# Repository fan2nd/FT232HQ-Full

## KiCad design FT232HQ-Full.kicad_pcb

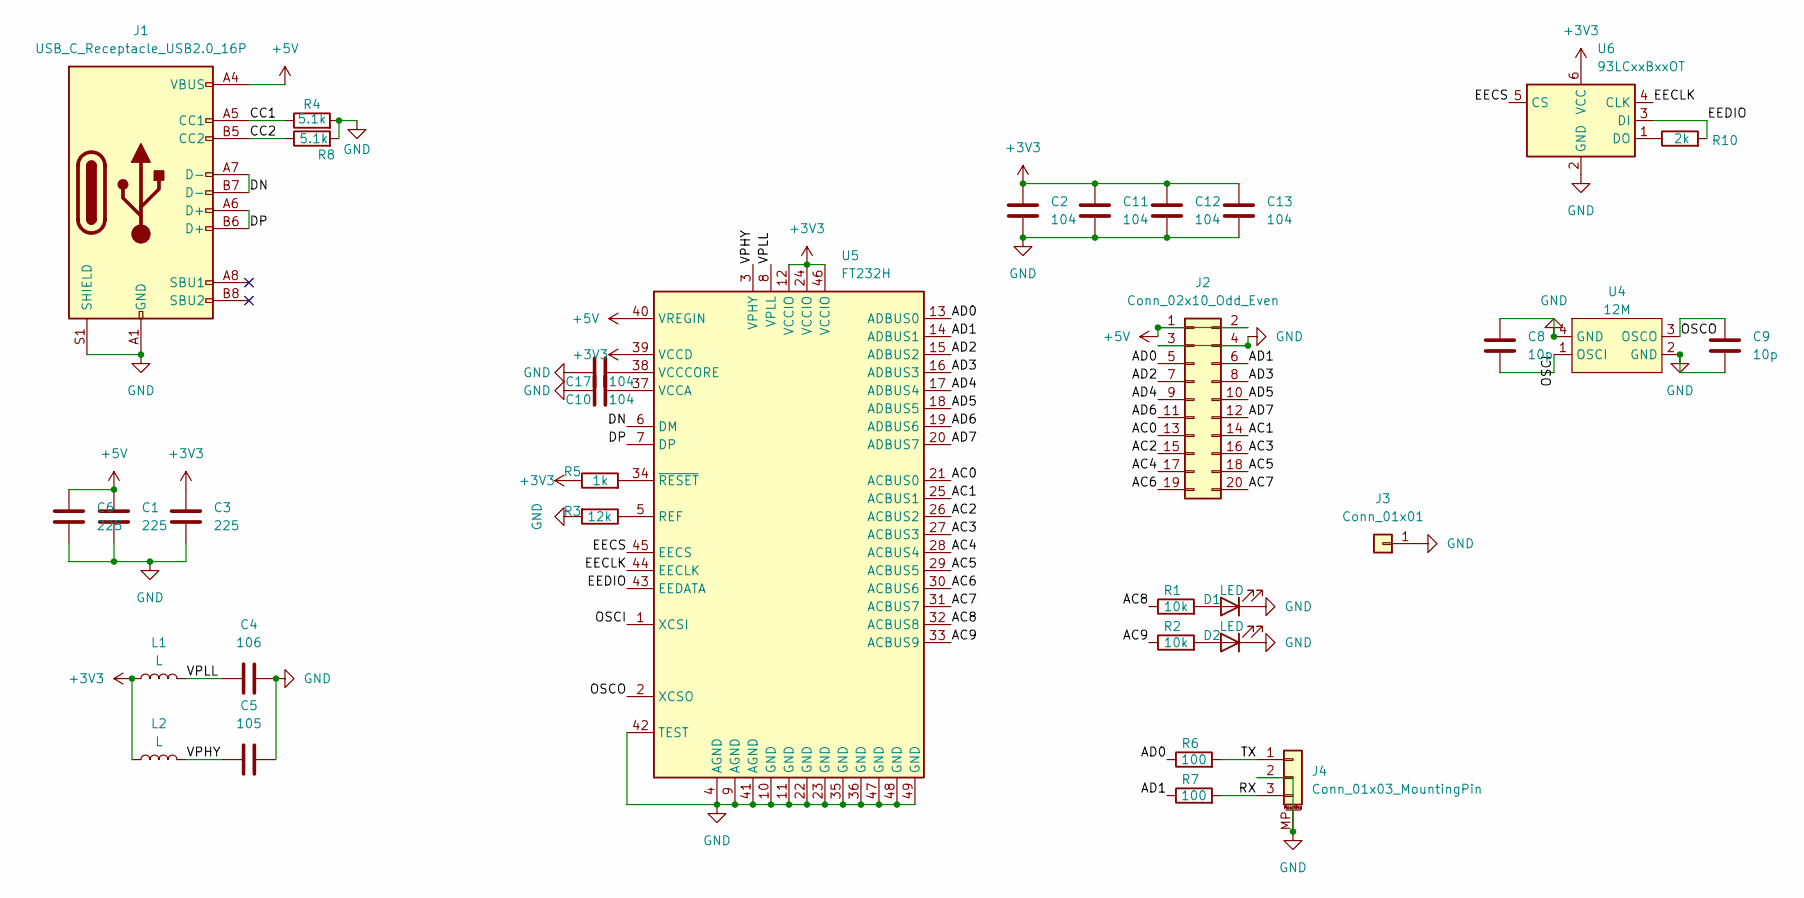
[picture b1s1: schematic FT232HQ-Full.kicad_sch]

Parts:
C1, C3, C6: 225; C_0402_1005Metric
C2, C10, C11, C12, C13, C17: 104; C_0402_1005Metric
C4: 106; C_0603_1608Metric
C5: 105; C_0603_1608Metric
C8, C9: 10p; C_0402_1005Metric
D1, D2: LED; LED_0402_1005Metric
J1: USB_C_Receptacle_USB2.0_16P; USB_C_Receptacle_TYPE-C-12P
J2: Conn_02x10_Odd_Even; PinHeader_2x10_P2.54mm_Vertical
J3: Conn_01x01; NUT_SMD_M2.5_4.5_3.0
J4: Conn_01x03_MountingPin; JST_SH_SM03B-SRSS-TB_1x03-1MP_P1.00mm_Horizontal
L1, L2: L; L_0603_1608Metric
R1, R2: 10k; R_0402_1005Metric
R3: 12k; R_0402_1005Metric
R4, R8: 5.1k; R_0402_1005Metric
R5: 1k; R_0402_1005Metric
R6, R7: 100; R_0402_1005Metric
R10: 2k; R_0402_1005Metric
U4: 12M; Oscillator_SMD_13_3.2x2.5mm
U5: FT232H; QFN-48-1EP_8x8mm_P0.5mm_EP6.2x6.2mm
U6: 93LCxxBxxOT; SOT-23-6

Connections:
+3V3: C2.1, C3.1, C11.1, C12.1, C13.1, L1.1, L2.1, R5.1, U5.12 (VCCIO), U5.24 (VCCIO), U5.39 (VCCD), U5.46 (VCCIO), U6.6 (VCC)
+5V: C1.1, C6.1, J1.A4 (VBUS), J1.A9 (VBUS), J1.B4 (VBUS), J1.B9 (VBUS), J2.1, J2.2, U5.40 (VREGIN)
/AC0: J2.13, U5.21 (ACBUS0)
/AC1: J2.14, U5.25 (ACBUS1)
/AC2: J2.15, U5.26 (ACBUS2)
/AC3: J2.16, U5.27 (ACBUS3)
/AC4: J2.17, U5.28 (ACBUS4)
/AC5: J2.18, U5.29 (ACBUS5)
/AC6: J2.19, U5.30 (ACBUS6)
/AC7: J2.20, U5.31 (ACBUS7)
/AC8: R1.1, U5.32 (ACBUS8)
/AC9: R2.1, U5.33 (ACBUS9)
/AD0: J2.5, R6.1, U5.13 (ADBUS0)
/AD1: J2.6, R7.1, U5.14 (ADBUS1)
/AD2: J2.7, U5.15 (ADBUS2)
/AD3: J2.8, U5.16 (ADBUS3)
/AD4: J2.9, U5.17 (ADBUS4)
/AD5: J2.10, U5.18 (ADBUS5)
/AD6: J2.11, U5.19 (ADBUS6)
/AD7: J2.12, U5.20 (ADBUS7)
/CC1: J1.A5 (CC1), R4.1
/CC2: J1.B5 (CC2), R8.1
/DN: J1.A7 (D-), J1.B7 (D-), U5.6 (DM)
/DP: J1.A6 (D+), J1.B6 (D+), U5.7 (DP)
/EECLK: U5.44 (EECLK), U6.4 (CLK)
/EECS: U5.45 (EECS), U6.5 (CS)
/EEDIO: R10.2, U5.43 (EEDATA), U6.3 (DI)
/OSCI: C8.2, U4.1 (OSCI), U5.1 (XCSI)
/OSCO: C9.2, U4.3 (OSCO), U5.2 (XCSO)
/RX: J4.3, R7.2
/TX: J4.1, R6.2
/VPHY: C5.1, L2.2, U5.3 (VPHY)
/VPLL: C4.1, L1.2, U5.8 (VPLL)
GND: C1.2, C2.2, C3.2, C4.2, C5.2, C6.2, C8.1, C9.1, C10.1, C11.2, C12.2, C13.2, C17.1, D1.1 (K), D2.1 (K), J1.A1 (GND), J1.A12 (GND), J1.B1 (GND), J1.B12 (GND), J1.S1 (SHIELD), J2.3, J2.4, J3.1, J4.2, J4.MP (MountPin), R3.2, R4.2, R8.2, U4.2 (GND), U4.4 (GND), U5.4 (AGND), U5.9 (AGND), U5.10 (GND), U5.11 (GND), U5.22 (GND), U5.23 (GND), U5.35 (GND), U5.36 (GND), U5.41 (AGND), U5.42 (TEST), U5.47 (GND), U5.48 (GND), U5.49 (GND), U6.2 (GND)
unnamed: D1.2 (A), R1.2
unnamed: D2.2 (A), R2.2
unnamed: R3.1, U5.5 (REF)
unnamed: C10.2, U5.37 (VCCA)
unnamed: C17.2, U5.38 (VCCCORE)
unnamed: R5.2, U5.34 (~RESET)
unnamed: R10.1, U6.1 (DO)

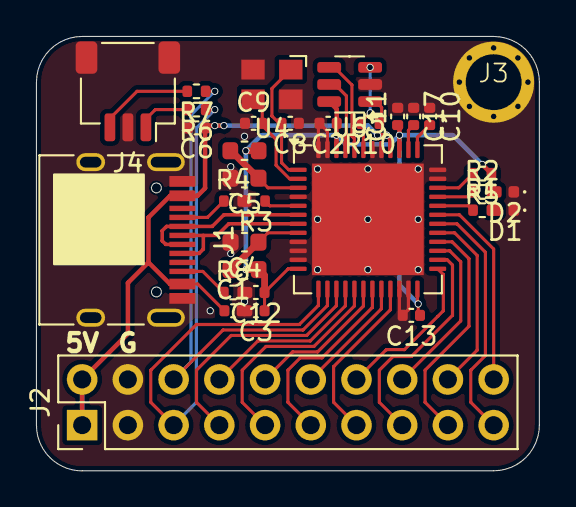
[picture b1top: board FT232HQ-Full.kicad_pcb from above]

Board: 2 copper layers, 27.9 x 24.1 mm, 33 parts (0 on the bottom side), 41 nets.

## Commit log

2025-02-27 add raspberrypi jst-sh1.0 uart
2025-02-27 add 2.2uf to 5v
